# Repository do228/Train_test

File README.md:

# 鉄道模型用リポジトリ

内容:
- [コントローラー基盤データ（回路）](controller_board)
- [コントローラー側ファームウェア](server_train)
- [電車側ファームウェア](client_train)

## 使い方

1. [コントローラー基盤データ（回路）](controller_board)を見て部品を集める。
2. コントローラー基盤に部品をはんだ付けで実装する。
3. プログラム上のMACアドレスを変更してコントローラーと電車模型のUUIDが一致するようにしてプログラムを書き込む。

## 必要な部品(コントローラー)

- LM1117GS-3.3(3端子レギュレーター)
- 1uFのコンデンサ
- ボリューム抵抗
- 10~20KΩの抵抗
- 1KΩの抵抗
- DCジャック
- OSL10564という型番の7セグメントLED
- 100Ω~20KΩ抵抗

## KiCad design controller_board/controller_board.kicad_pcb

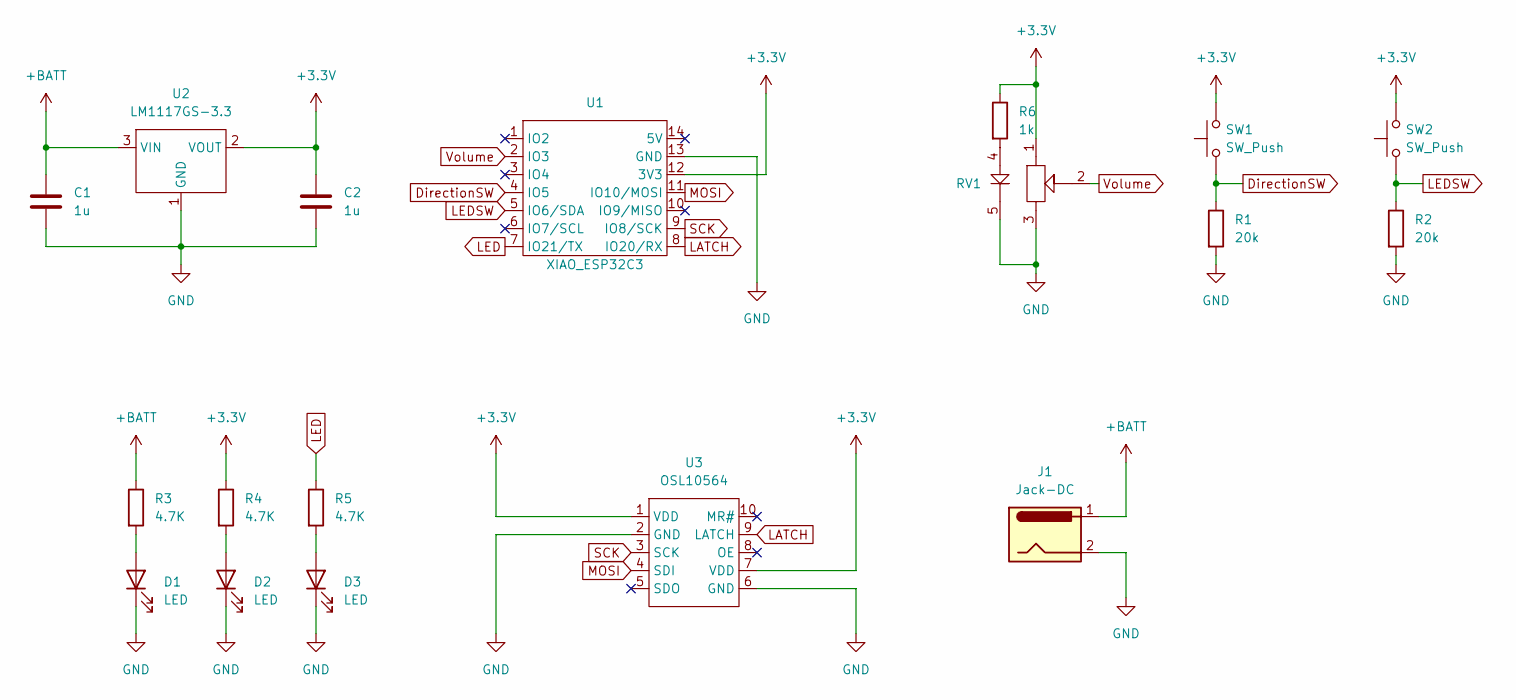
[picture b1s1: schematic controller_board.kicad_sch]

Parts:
C1, C2: 1u; C_Disc_D5.0mm_W2.5mm_P5.00mm
D1, D2, D3: LED; LED_D3.0mm
J1: Jack-DC; DCJack2.1
R1, R2: 20k; R_Axial_DIN0204_L3.6mm_D1.6mm_P7.62mm_Horizontal
R3, R4, R5: 4.7K; R_Axial_DIN0204_L3.6mm_D1.6mm_P7.62mm_Horizontal
R6: 1k; R_Axial_DIN0204_L3.6mm_D1.6mm_P7.62mm_Horizontal
RV1: VR-sliderV2
SW1, SW2: SW_Push; PinHeader_1x02_P2.54mm_Vertical
U1: XIAO_ESP32C3
U2: LM1117GS-3.3; SOT-223-3_TabPin2
U3: OSL10564; OSL10564-MODULE

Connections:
+3.3V: C2.1, R4.1, R6.1, RV1.1, SW1.2, SW2.2, U1.12 (3V3), U2.2 (VOUT), U3.1 (VDD), U3.7 (VDD)
+BATT: C1.1, J1.1, R3.1, U2.3 (VIN)
DirectionSW: R1.1, SW1.1, U1.4 (IO5)
GND: C1.2, C2.2, D1.1 (K), D2.1 (K), D3.1 (K), J1.2, R1.2, R2.2, RV1.3, RV1.5, U1.13 (GND), U2.1 (GND), U3.2 (GND), U3.6 (GND)
LATCH: U1.8 (IO20/RX), U3.9 (LATCH)
LED: R5.1, U1.7 (IO21/TX)
LEDSW: R2.1, SW2.1, U1.5 (IO6/SDA)
MOSI: U1.11 (IO10/MOSI), U3.4 (SDI)
unnamed: D1.2 (A), R3.2
unnamed: D2.2 (A), R4.2
unnamed: D3.2 (A), R5.2
unnamed: R6.2, RV1.4
SCK: U1.9 (IO8/SCK), U3.3 (SCK)
Volume: RV1.2, U1.2 (IO3)

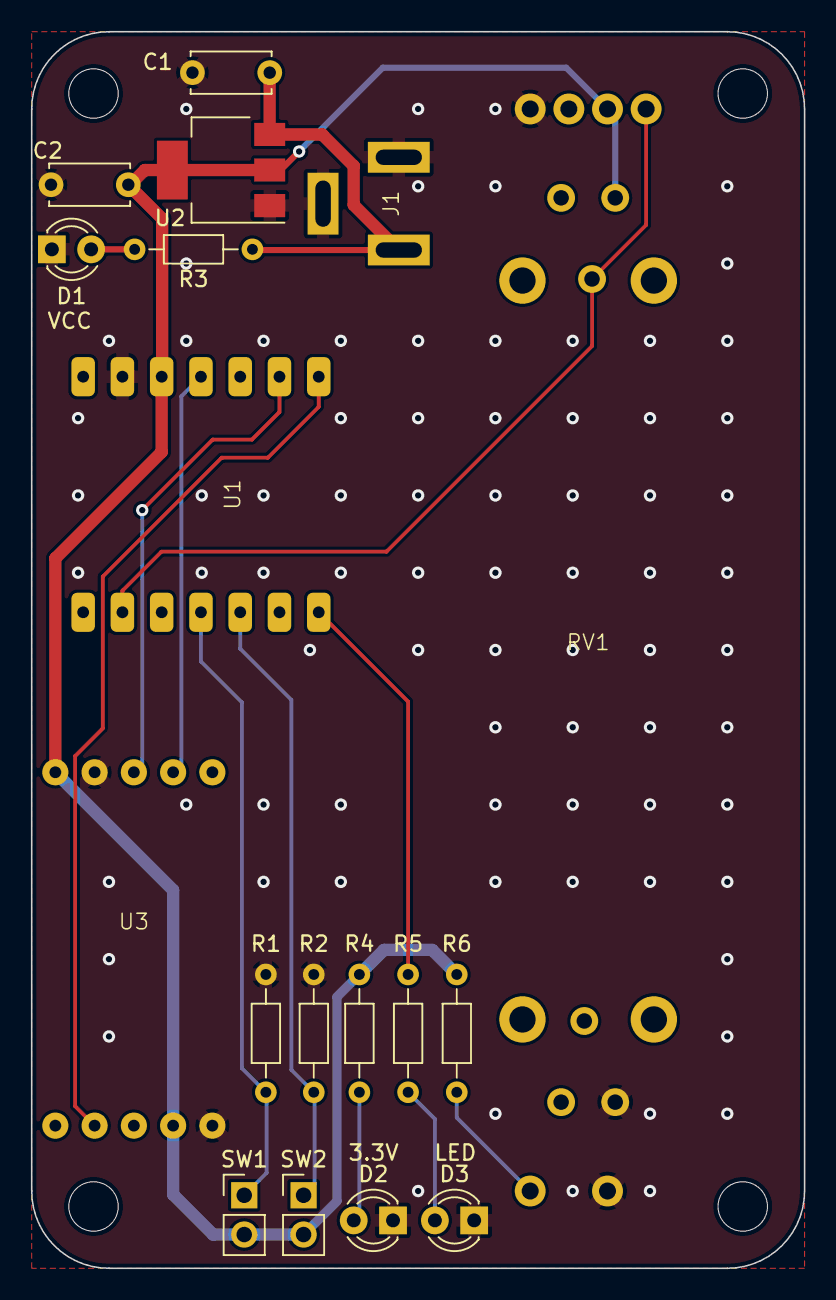
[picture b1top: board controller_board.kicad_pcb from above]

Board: 2 copper layers, 50.0 x 80.0 mm, 18 parts (0 on the bottom side), 14 nets.

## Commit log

2023-09-29 UUIDのバリエーションを追加。7セグのプログラムの完成
2024-04-14 PCB-now
2024-04-14 README追加
2024-04-14 自動整形
2024-04-14 コメント追加
2024-04-14 READMEのfix
2024-04-14 gitignore
2024-04-14 必要なものリスト追加
